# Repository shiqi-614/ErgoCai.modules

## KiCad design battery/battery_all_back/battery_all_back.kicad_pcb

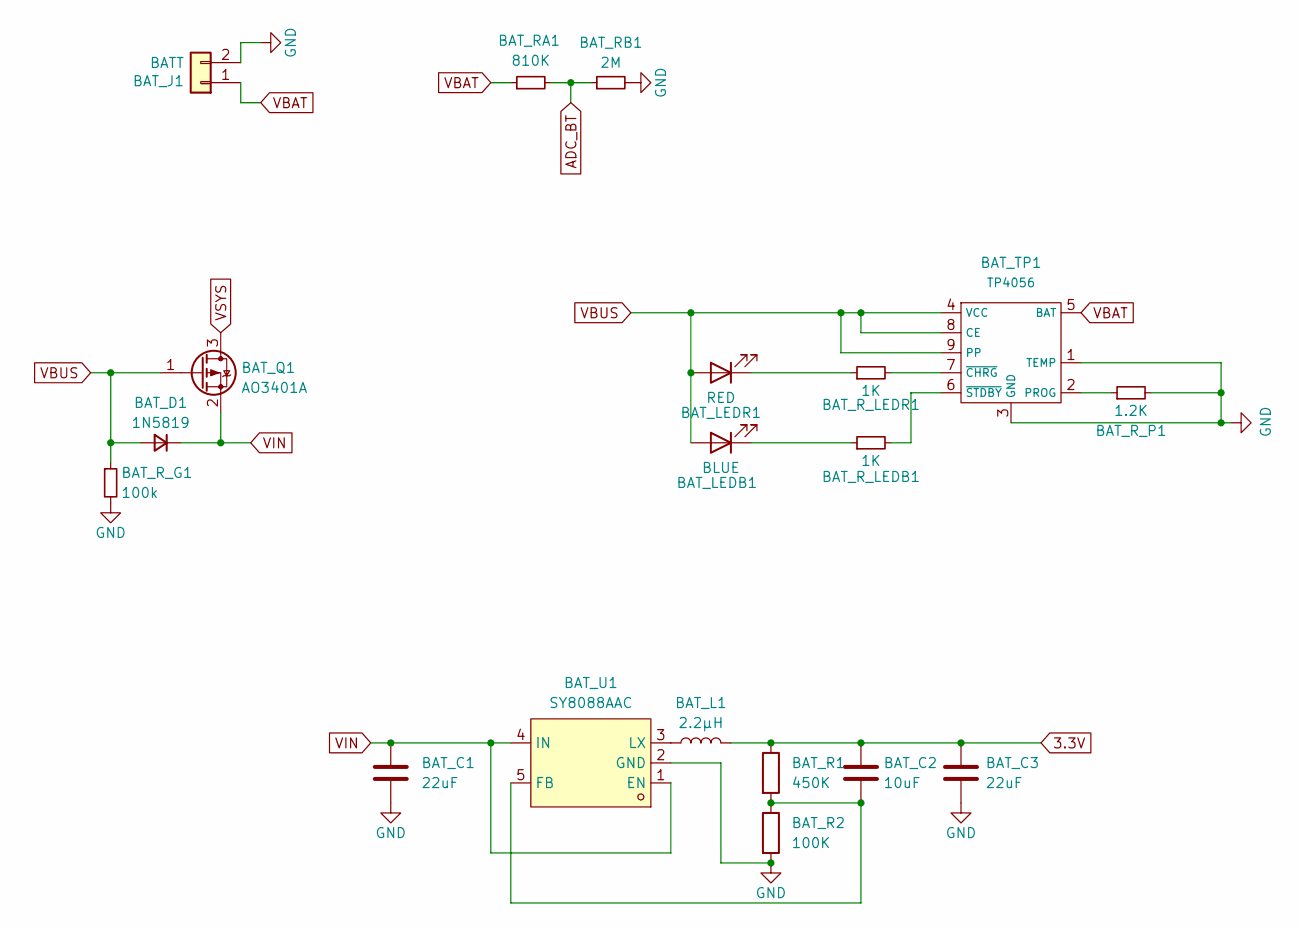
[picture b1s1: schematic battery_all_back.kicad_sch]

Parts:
BAT_C1, BAT_C3: 22uF; C_0603_1608Metric
BAT_C2: 10uF; C_0603_1608Metric
BAT_D1: 1N5819; D_SOD-123
BAT_J1: BATT; Battery_Holder_18650_Nickel
BAT_L1: 2.2µH; L_0603_1608Metric
BAT_LEDB1: BLUE; LED_0603_1608Metric
BAT_LEDR1: RED; LED_0603_1608Metric
BAT_Q1: AO3401A; SOT-23
BAT_R1: 450K; R_0603_1608Metric
BAT_R2: 100K; R_0603_1608Metric
BAT_RA1: 810K; R_0603_1608Metric
BAT_RB1: 2M; R_0603_1608Metric
BAT_R_G1: 100k; R_0603_1608Metric
BAT_R_LEDB1: 1K; R_0603_1608Metric
BAT_R_LEDR1: 1K; R_0603_1608Metric
BAT_R_P1: 1.2K; R_0603_1608Metric
BAT_TP1: TP4056; SOIC-8-1EP_3.9x4.9mm_P1.27mm_EP2.29x3mm
BAT_U1: SY8088AAC; SOT-23-5_L3.0-W1.7-P0.95-LS2.8-BR; LCSC Part C79313

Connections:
3.3V: BAT_C2.1, BAT_C3.1, BAT_L1.2, BAT_R1.1
ADC_BT: BAT_RA1.2, BAT_RB1.1
GND: BAT_C1.2, BAT_C3.2, BAT_J1.2, BAT_R2.2, BAT_RB1.2, BAT_R_G1.2, BAT_R_P1.2, BAT_TP1.1 (TEMP), BAT_TP1.3 (GND), BAT_U1.2 (GND)
unnamed: BAT_LEDB1.1 (K), BAT_R_LEDB1.1
unnamed: BAT_LEDR1.1 (K), BAT_R_LEDR1.1
unnamed: BAT_R_P1.1, BAT_TP1.2 (PROG)
unnamed: BAT_R_LEDR1.2, BAT_TP1.7 (~CHRG)
unnamed: BAT_R_LEDB1.2, BAT_TP1.6 (~STDBY)
unnamed: BAT_C2.2, BAT_R1.2, BAT_R2.1, BAT_U1.5 (FB)
unnamed: BAT_L1.1, BAT_U1.3 (LX)
VBAT: BAT_J1.1, BAT_RA1.1, BAT_TP1.5 (BAT)
VBUS: BAT_D1.2 (A), BAT_LEDB1.2 (A), BAT_LEDR1.2 (A), BAT_Q1.1 (G), BAT_R_G1.1, BAT_TP1.4 (VCC), BAT_TP1.8 (CE), BAT_TP1.9 (PP)
VIN: BAT_C1.1, BAT_D1.1 (K), BAT_Q1.2 (S), BAT_U1.1 (EN), BAT_U1.4 (IN)
VSYS: BAT_Q1.3 (D)

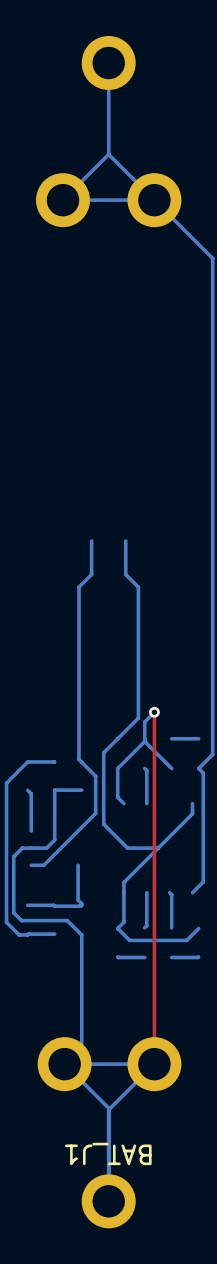
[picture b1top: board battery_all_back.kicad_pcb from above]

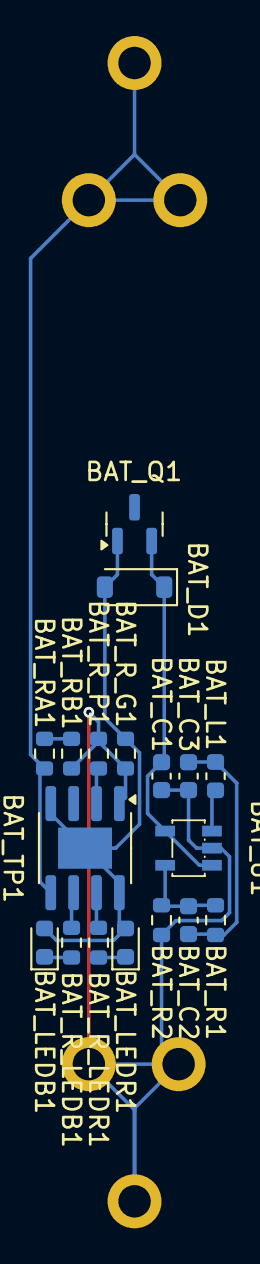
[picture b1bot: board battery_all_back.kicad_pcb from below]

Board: 2 copper layers, 19 parts (18 on the bottom side), 13 nets.

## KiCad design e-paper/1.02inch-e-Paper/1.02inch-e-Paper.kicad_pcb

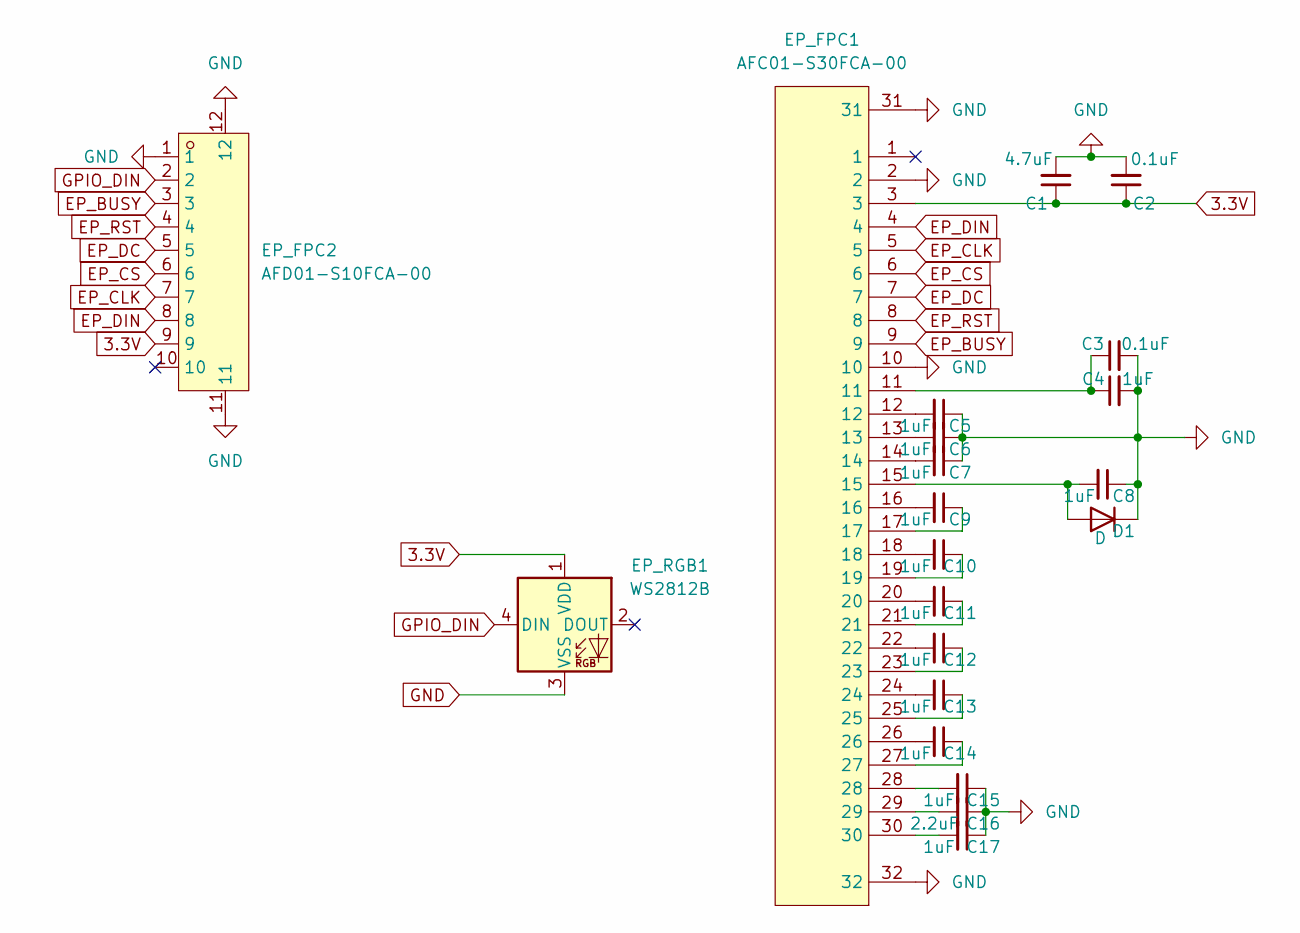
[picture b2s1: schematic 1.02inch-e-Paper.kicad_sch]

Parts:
C1: 4.7uF; C_0603_1608Metric
C2, C3: 0.1uF; C_0603_1608Metric
C4, C5, C6, C7, C8, C9, C10, C11, C12, C13, C14, C15, C17: 1uF; C_0603_1608Metric
C16: 2.2uF; C_0603_1608Metric
D1: D; D_SOD-123
EP_FPC1: AFC01-S30FCA-00; FPC-SMD_AFC01-S30FCA-00; LCSC Part C262671
EP_FPC2: AFD01-S10FCA-00; FPC-SMD_10P-P0.50_JS_AFD01-S10FCA-00; LCSC Part C18198578
EP_RGB1: WS2812B; LED-SMD_4P-L5.0-W5.0-TL_WS2812B-B

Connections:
3.3V: C1.1, C2.1, EP_FPC1.3, EP_FPC2.9, EP_RGB1.1 (VDD)
EP_BUSY: EP_FPC1.9, EP_FPC2.3
EP_CLK: EP_FPC1.5, EP_FPC2.7
EP_CS: EP_FPC1.6, EP_FPC2.6
EP_DC: EP_FPC1.7, EP_FPC2.5
EP_DIN: EP_FPC1.4, EP_FPC2.8
EP_RST: EP_FPC1.8, EP_FPC2.4
GND: C1.2, C2.2, C3.2, C4.2, C5.1, C6.1, C7.1, C8.1, C15.1, C16.1, C17.1, D1.1 (K), EP_FPC1.2, EP_FPC1.10, EP_FPC1.31, EP_FPC1.32, EP_FPC2.1, EP_FPC2.11, EP_FPC2.12, EP_RGB1.3 (VSS)
GPIO_DIN: EP_FPC2.2, EP_RGB1.4 (DIN)
unnamed: C3.1, C4.1, EP_FPC1.11
unnamed: C5.2, EP_FPC1.12
unnamed: C6.2, EP_FPC1.13
unnamed: C7.2, EP_FPC1.14
unnamed: C9.1, EP_FPC1.17
unnamed: C9.2, EP_FPC1.16
unnamed: C10.1, EP_FPC1.19
unnamed: C10.2, EP_FPC1.18
unnamed: C11.1, EP_FPC1.21
unnamed: C11.2, EP_FPC1.20
unnamed: C12.1, EP_FPC1.23
unnamed: C12.2, EP_FPC1.22
unnamed: C13.1, EP_FPC1.25
unnamed: C13.2, EP_FPC1.24
unnamed: C14.1, EP_FPC1.27
unnamed: C14.2, EP_FPC1.26
unnamed: C15.2, EP_FPC1.28
unnamed: C16.2, EP_FPC1.29
unnamed: C17.2, EP_FPC1.30
unnamed: C8.2, D1.2 (A), EP_FPC1.15

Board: 2 copper layers, 21 parts (20 on the bottom side), 29 nets, no tracks yet.

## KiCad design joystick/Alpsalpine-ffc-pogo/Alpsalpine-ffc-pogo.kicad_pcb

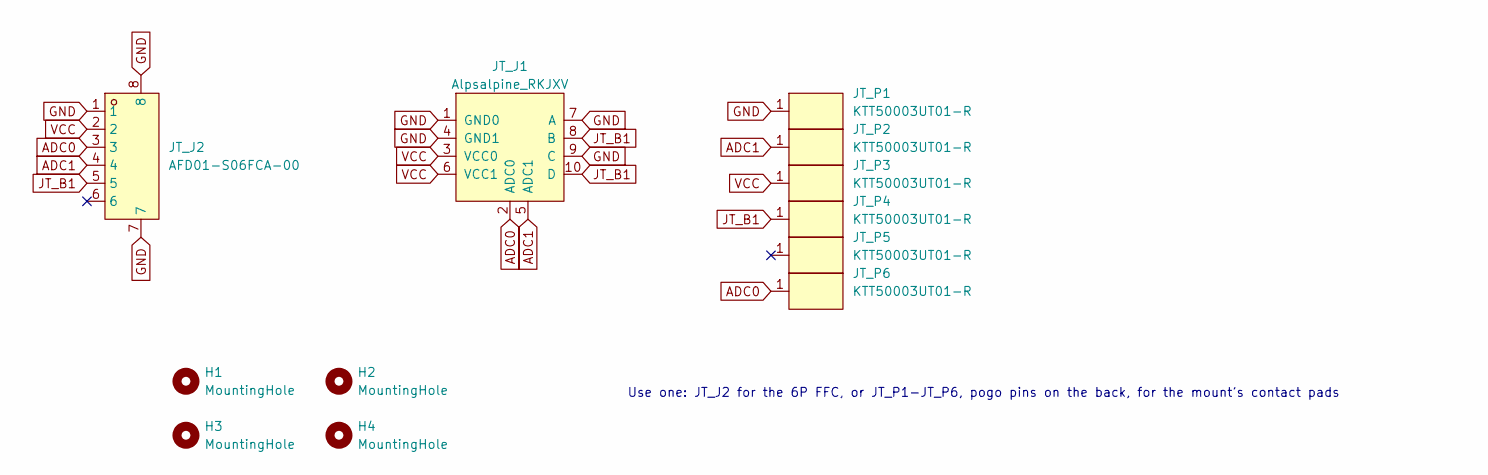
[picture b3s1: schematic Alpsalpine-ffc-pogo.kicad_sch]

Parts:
H1, H2, H3, H4: MountingHole; MountingHole_2.2mm_M2_DIN965
JT_J1: Alpsalpine_RKJXV; Alpsalpine_RKJXV122400R; LCSC C918854
JT_J2: AFD01-S06FCA-00; FPC-SMD_6P-P0.50_JS_AFD01-S06FCA-00; LCSC Part C18198574
JT_P1, JT_P2, JT_P3, JT_P4, JT_P5, JT_P6: KTT50003UT01-R; Pogo_KTT50003UT01-R; LCSC Part C56282211

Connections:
ADC0: JT_J1.2 (ADC0), JT_J2.3, JT_P6.1
ADC1: JT_J1.5 (ADC1), JT_J2.4, JT_P2.1
GND: JT_J1.1 (GND0), JT_J1.4 (GND1), JT_J1.7 (A), JT_J1.9 (C), JT_J2.1, JT_J2.7, JT_J2.8, JT_P1.1
JT_B1: JT_J1.8 (B), JT_J1.10 (D), JT_J2.5, JT_P4.1
VCC: JT_J1.3 (VCC0), JT_J1.6 (VCC1), JT_J2.2, JT_P3.1

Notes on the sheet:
Use one: JT_J2 for the 6P FFC, or JT_P1-JT_P6, pogo pins on the back, for the mount's contact pads

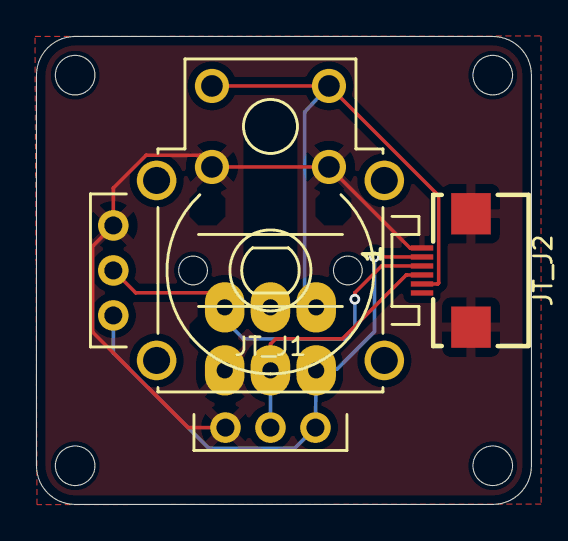
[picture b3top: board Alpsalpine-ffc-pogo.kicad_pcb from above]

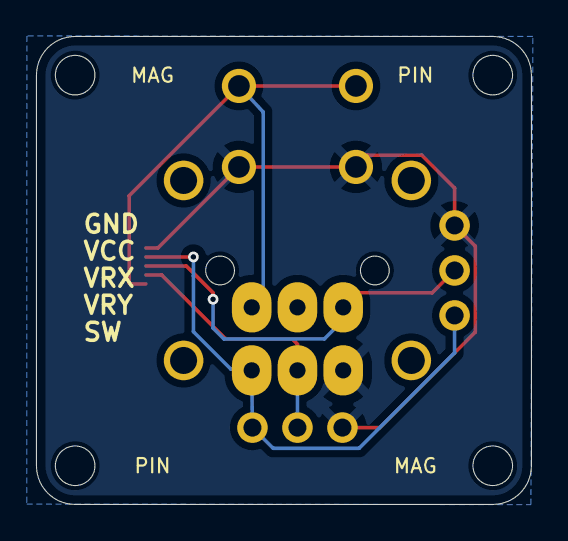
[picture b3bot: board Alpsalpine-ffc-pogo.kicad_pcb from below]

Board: 2 copper layers, 27.5 x 26.0 mm, 12 parts (6 on the bottom side), 5 nets.
